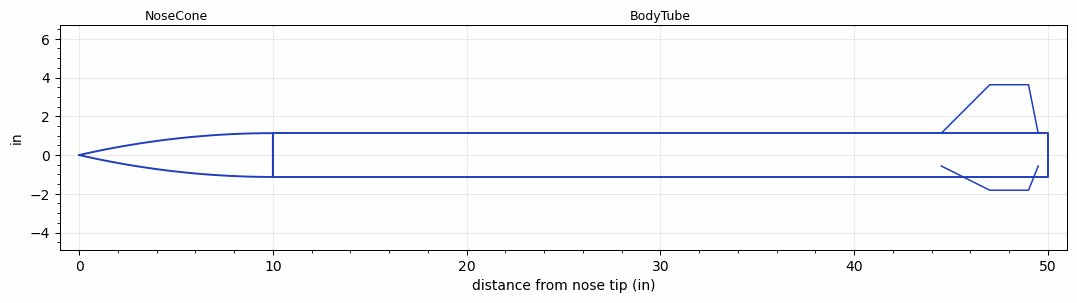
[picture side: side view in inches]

<RASAeroDocument>
 <FileVersion>2</FileVersion>
 <RocketDesign>
  <NoseCone>
   <Length>10</Length>
   <Diameter>2.26</Diameter>
   <Shape>Tangent Ogive</Shape>
   <Location>0</Location>
  </NoseCone>
  <BodyTube>
   <Length>39.9999</Length>
   <Diameter>2.26</Diameter>
   <Location>10</Location>
   <Fin>
    <Count>3</Count>
    <Chord>5</Chord>
    <Span>2.5</Span>
    <SweepDistance>2.5</SweepDistance>
    <TipChord>2</TipChord>
    <Thickness>0.125</Thickness>
    <Location>5.5</Location>
    <AirfoilSection>Hexagonal Blunt Base</AirfoilSection>
    <FX1>0.25</FX1>
   </Fin>
  </BodyTube>
  <Surface>Smooth (Zero Roughness)</Surface>
  <ModifiedBarrowman>False</ModifiedBarrowman>
  <Turbulence>False</Turbulence>
  <UseBooster1>False</UseBooster1>
  <UseBooster2>False</UseBooster2>
  <Comments>Extended controlled aerodynamic study: Sbev-transition</Comments>
 </RocketDesign>
 <LaunchSite>
  <Altitude>0</Altitude>
  <Pressure>29.9214</Pressure>
  <RodAngle>0</RodAngle>
  <RodLength>6.5617</RodLength>
  <Temperature>59</Temperature>
  <WindSpeed>0</WindSpeed>
 </LaunchSite>
 <Recovery>
  <Altitude1>656.168</Altitude1>
  <Altitude2>0</Altitude2>
  <DeviceType1>Parachute</DeviceType1>
  <DeviceType2>None</DeviceType2>
  <Event1>True</Event1>
  <Event2>False</Event2>
  <Size1>24</Size1>
  <Size2>0</Size2>
  <EventType1>Apogee</EventType1>
  <EventType2>None</EventType2>
  <CD1>0.8</CD1>
  <CD2>0</CD2>
 </Recovery>
 <SimulationList>
  <Simulation>
   <SustainerEngine>I500T-14A  (AT)</SustainerEngine>
   <SustainerLaunchWt>3.4833</SustainerLaunchWt>
   <SustainerCG>32.8777</SustainerCG>
   <SustainerIgnitionDelay>0</SustainerIgnitionDelay>
   <Booster1SeparationDelay>0</Booster1SeparationDelay>
   <Booster1IgnitionDelay>0</Booster1IgnitionDelay>
   <IncludeBooster1>False</IncludeBooster1>
   <Booster2Delay>0</Booster2Delay>
   <IncludeBooster2>False</IncludeBooster2>
   <TimetoApogee>17.96032</TimetoApogee>
   <MaxAltitude>7243.022</MaxAltitude>
   <MaxVelocity>1209.051</MaxVelocity>
  </Simulation>
  <Simulation>
   <SustainerEngine>J570W  (AT)</SustainerEngine>
   <SustainerLaunchWt>4.1582</SustainerLaunchWt>
   <SustainerCG>33.3758</SustainerCG>
   <SustainerIgnitionDelay>0</SustainerIgnitionDelay>
   <Booster1SeparationDelay>0</Booster1SeparationDelay>
   <Booster1IgnitionDelay>0</Booster1IgnitionDelay>
   <IncludeBooster1>False</IncludeBooster1>
   <Booster2Delay>0</Booster2Delay>
   <IncludeBooster2>False</IncludeBooster2>
   <TimetoApogee>19.43035</TimetoApogee>
   <MaxAltitude>9304.529</MaxAltitude>
   <MaxVelocity>1521.587</MaxVelocity>
  </Simulation>
 </SimulationList>
</RASAeroDocument>
